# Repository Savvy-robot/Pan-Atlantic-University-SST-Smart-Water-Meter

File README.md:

# Pan-Atlantic-University-SST-Smart-Water-Meter
Certainly! Here's an updated version of the project statement, incorporating the additional information:

---

## Project Description: Smart Water Meter for Rural Communities

### Introduction
The Smart Water Meter is an innovative project proposed by the engineering faculty of Pan Atlantic University for the external competition involvng different universities in Nigeria. The aim of this project is to address the pressing issue of water scarcity and uneven distribution in rural communities. By leveraging advanced technologies, the Smart Water Meter offers an efficient solution that ensures fair and adequate water supply to these underserved areas.

### Problem Statement
Many rural communities face challenges when it comes to accessing good quality water. Unequal distribution, inefficient usage, and lack of monitoring systems contribute to water scarcity and the subsequent hardships faced by the residents. Traditional water management methods are often manual, time-consuming, and prone to errors, making it difficult to achieve equitable water distribution.

### Solution: Smart Water Meter
The Smart Water Meter is an automated water management system designed to promote sustainable water usage and ensure fair distribution in rural communities. It incorporates cutting-edge technology to provide accurate monitoring, efficient usage tracking, and remote management capabilities.

### Key Features

1. **Real-time Monitoring**: The Smart Water Meter tracks water consumption in real-time, enabling accurate and up-to-date data on water usage. This information is crucial for efficient management and effective decision-making.

2. **Remote Management**: The system allows for remote management, enabling administrators to monitor and control water distribution without physically visiting each location. This remote functionality greatly reduces operational costs and enhances convenience.

3. **Rationing and Fair Distribution**: The Smart Water Meter employs intelligent algorithms to analyze water consumption patterns and implement rationing strategies. This ensures that water is distributed fairly among all households, mitigating water scarcity and promoting equity.

4. **Leak Detection**: By continuously monitoring water flow and consumption, the system can quickly detect and alert users and administrators about any leaks or abnormalities. This feature helps minimize water wastage and prevents damage to the water infrastructure.

5. **Data Analytics and Insights**: The collected data can be analyzed to gain valuable insights into water consumption patterns, identify areas for improvement, and optimize resource allocation. These analytics enable evidence-based decision-making and long-term planning.

### Your Contribution as an Embedded Systems Developer
As an undergraduate in my Hundred level, I played a significant role as the Embedded Systems Developer for the Smart Water Meter project. I was responsible for designing the circuit schematics and developing the Printed Circuit Board (PCB) that forms the core of the system.

By utilizing my expertise in embedded systems development, I successfully translated the project requirements into a practical circuit design. This involved meticulous selection of microcontrollers, sensors, and communication modules to enable real-time monitoring and remote management capabilities. My diligent work in designing the circuit schematics and fabricating the PCB significantly contributed to the overall success and functionality of the Smart Water Meter.

Through my dedication and commitment to learning, I exemplify a passion for technology and the ability to make meaningful contributions to projects with tangible real-world impact.

### Benefits
- **Equitable Water Distribution**: The Smart Water Meter ensures fair and even distribution of water among rural communities, reducing water scarcity and improving the quality of life.
- **Water Conservation**: By monitoring usage and detecting leaks, the system promotes efficient water usage and helps prevent wastage, leading to the conservation of this precious resource.
- **Cost Savings**: The ability to remotely manage and monitor water supply reduces operational costs and improves the efficiency of water management processes.
- **Data-Driven Decision Making**: The system provides valuable insights through data analytics, enabling informed decisions, resource optimization, and effective long-term planning.

### Conclusion
The Smart Water Meter project proposed by the engineering faculty of Pan Atlantic University, along with my contribution as the Embedded Systems Developer, offers an innovative solution to address water scarcity and unequal distribution in rural communities. Through the integration of advanced technologies, real-time monitoring, and remote management capabilities, the project aims to provide reliable and equitable water supply, thereby significantly improving the lives of rural residents.

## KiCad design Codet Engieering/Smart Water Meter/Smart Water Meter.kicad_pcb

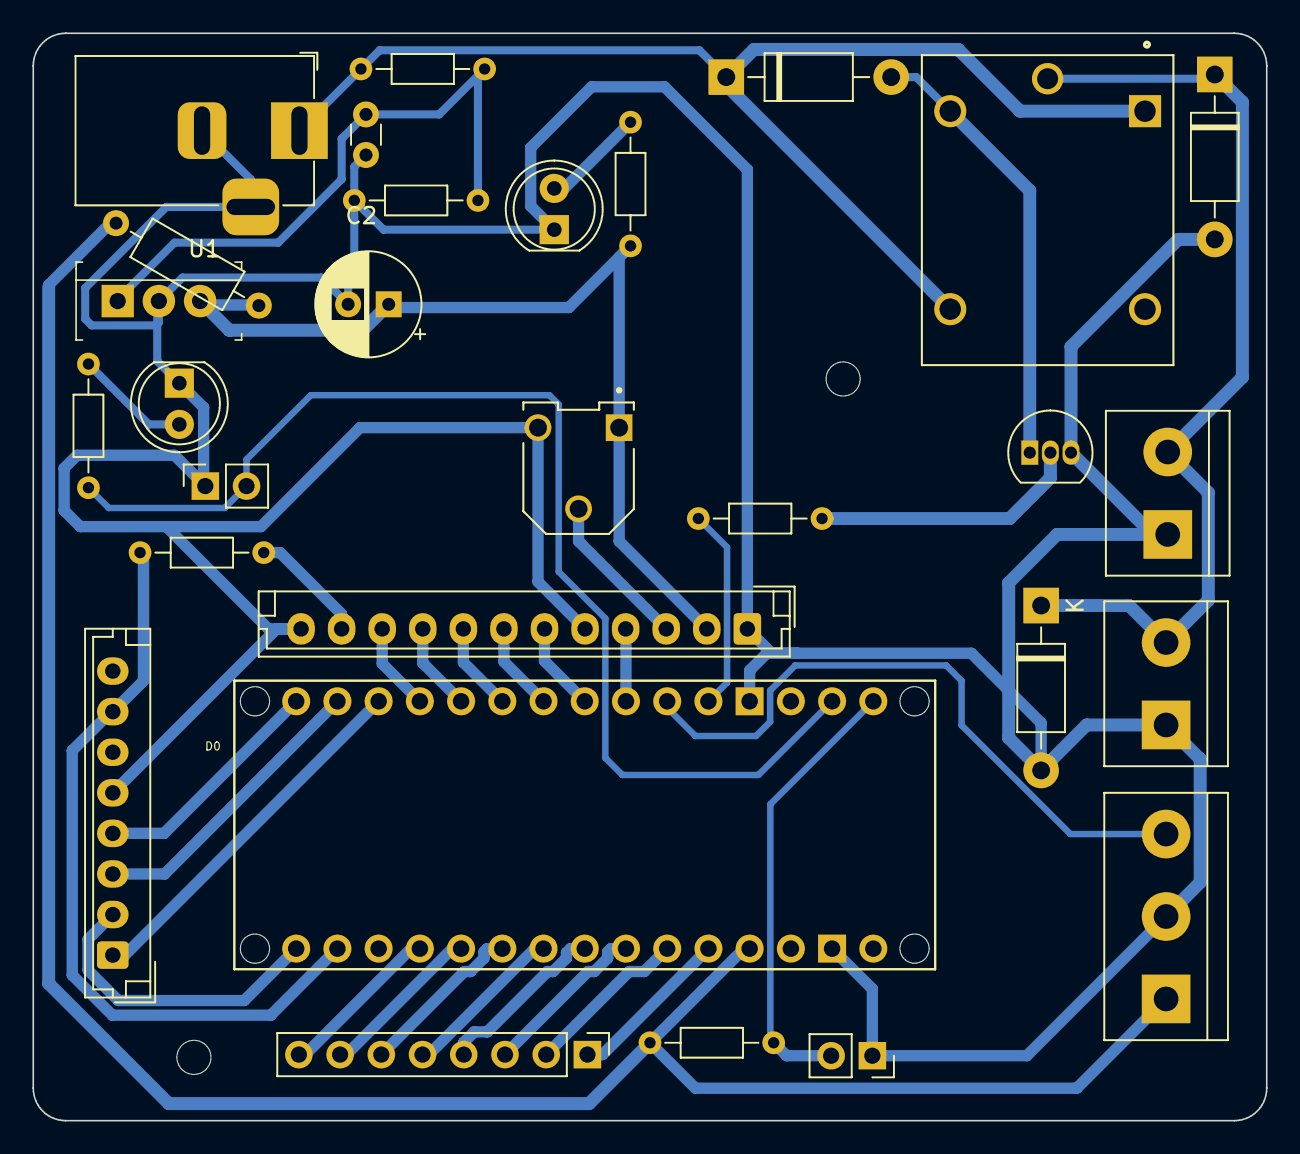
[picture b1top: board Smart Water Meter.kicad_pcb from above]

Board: 2 copper layers, 76.0 x 67.0 mm, 31 parts (0 on the bottom side), 34 nets.

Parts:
C1: 0.1uF; C_Disc_D3.0mm_W1.6mm_P2.50mm
C2: 220uF; CP_Radial_D6.3mm_P2.50mm
D1, D4, D5: 1N4007; D_DO-41_SOD81_P10.16mm_Horizontal
D2, D3: LED; LED_D5.0mm
H1, H2: MountingHole; MountingHole_2.1mm
J1: Barrel_Jack_Switch; BarrelJack_Horizontal
J2, J7: Screw_Terminal_01x02; TerminalBlock_bornier-2_P5.08mm
J3: Conn_01x12_Pin; JST_EH_B12B-EH-A_1x12_P2.50mm_Vertical
J4: Conn_01x07_Pin; PinHeader_1x08_P2.54mm_Vertical
J5: Conn_01x08_Pin; JST_EH_B8B-EH-A_1x08_P2.50mm_Vertical
J6: Screw_Terminal_01x03; TerminalBlock_bornier-3_P5.08mm
JP1, JP2: Jumper_2_Open; PinSocket_1x02_P2.54mm_Vertical
Jumper: 220R; R_Axial_DIN0207_L6.3mm_D2.5mm_P10.16mm_Horizontal
K1: SRD-05VDC-SL-C; RELAY_SRD-05VDC-SL-C
Q1: BC547; TO-92_Inline
R1, R4, R7: R; R_Axial_DIN0204_L3.6mm_D1.6mm_P7.62mm_Horizontal
R2: 330R; R_Axial_DIN0204_L3.6mm_D1.6mm_P7.62mm_Horizontal
R3, R6: 220R; R_Axial_DIN0204_L3.6mm_D1.6mm_P7.62mm_Horizontal
R5: 1K; R_Axial_DIN0204_L3.6mm_D1.6mm_P7.62mm_Horizontal
RV1: 10K; TRIM_3306F-1-103
U1: L7805CV; TO-220-3
XA1: Arduino_Nano_Every_Socket

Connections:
5V: C2.1, J3.2, J6.1, Jumper.1, Jumper.2, R2.1, R7.1, RV1.1, U1.3 (OUT), XA1.5V
12V: D1.1 (K), J1.1, K1.A1, K1.NO, R1.1
Buzzer: JP2.2 (B), R3.1, XA1.D0 (D0/RX)
GND: C1.2, C2.2, D2.1 (K), D3.1 (K), D4.2 (A), D5.2 (A), J1.2, J1.3, J2.1, J3.1, J3.5, J3.12, J5.5, J6.2, J7.1, JP1.1 (A), JP2.1 (A), Q1.3 (E), R4.2, RV1.3, U1.2 (GND), XA1.GND1 (GND), XA1.GND2 (GND)
unnamed: D1.2 (A), K1.A2, Q1.1 (C)
unnamed: D2.2 (A), R2.2
unnamed: D3.2 (A), R3.2
unnamed: D4.1 (K), D5.1 (K), J2.2, J7.2, K1.COM
unnamed: J3.3, RV1.2
unnamed: J3.4, XA1.D4
unnamed: J3.6, XA1.D5
unnamed: J3.7, XA1.D6
unnamed: J3.8, XA1.D7
unnamed: J3.9, XA1.D8
unnamed: J3.10, XA1.D9
unnamed: J3.11, R6.1
unnamed: J4.1, XA1.A7
unnamed: J4.2, XA1.A6
unnamed: J4.3, XA1.A5 (A5/SCL)
unnamed: J4.4, XA1.A4 (A4/SDA)
unnamed: J4.5, XA1.A3
unnamed: J4.6, XA1.A2
unnamed: J4.7, XA1.A1
unnamed: J4.8, XA1.A0
unnamed: J5.1, XA1.D10
unnamed: J5.2, XA1.D13 (D13_SCK)
unnamed: J5.3, XA1.D11 (D11_MOSI)
unnamed: J5.4, XA1.D12 (D12_MISO)
unnamed: J5.7, R6.2, XA1.3V3 (3.3V)
unnamed: Q1.2 (B), R5.1
unnamed: C1.1, R1.2, R4.1, U1.1 (IN)
PUMP CONTROL: R5.2, XA1.D2
SIGNAL: J6.3, XA1.D3
START: JP1.2 (B), R7.2, XA1.D1 (D1/TX)

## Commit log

2023-06-13 Started the design thinking process and made a visual schematic for easy connection and then made the production PCB schematics and footprint
2023-06-15 Redessigned the board to fit into asingle layer pcb for local production
2023-06-15 Deleted the numerous backup files from the folder
2023-06-15 Sorted the diferent files inot a new folder and also removed some unnecessary files from the repository
2023-06-15 Edited a document name
2023-06-15 Initialized gitignore and kept some unwanted tracked files
